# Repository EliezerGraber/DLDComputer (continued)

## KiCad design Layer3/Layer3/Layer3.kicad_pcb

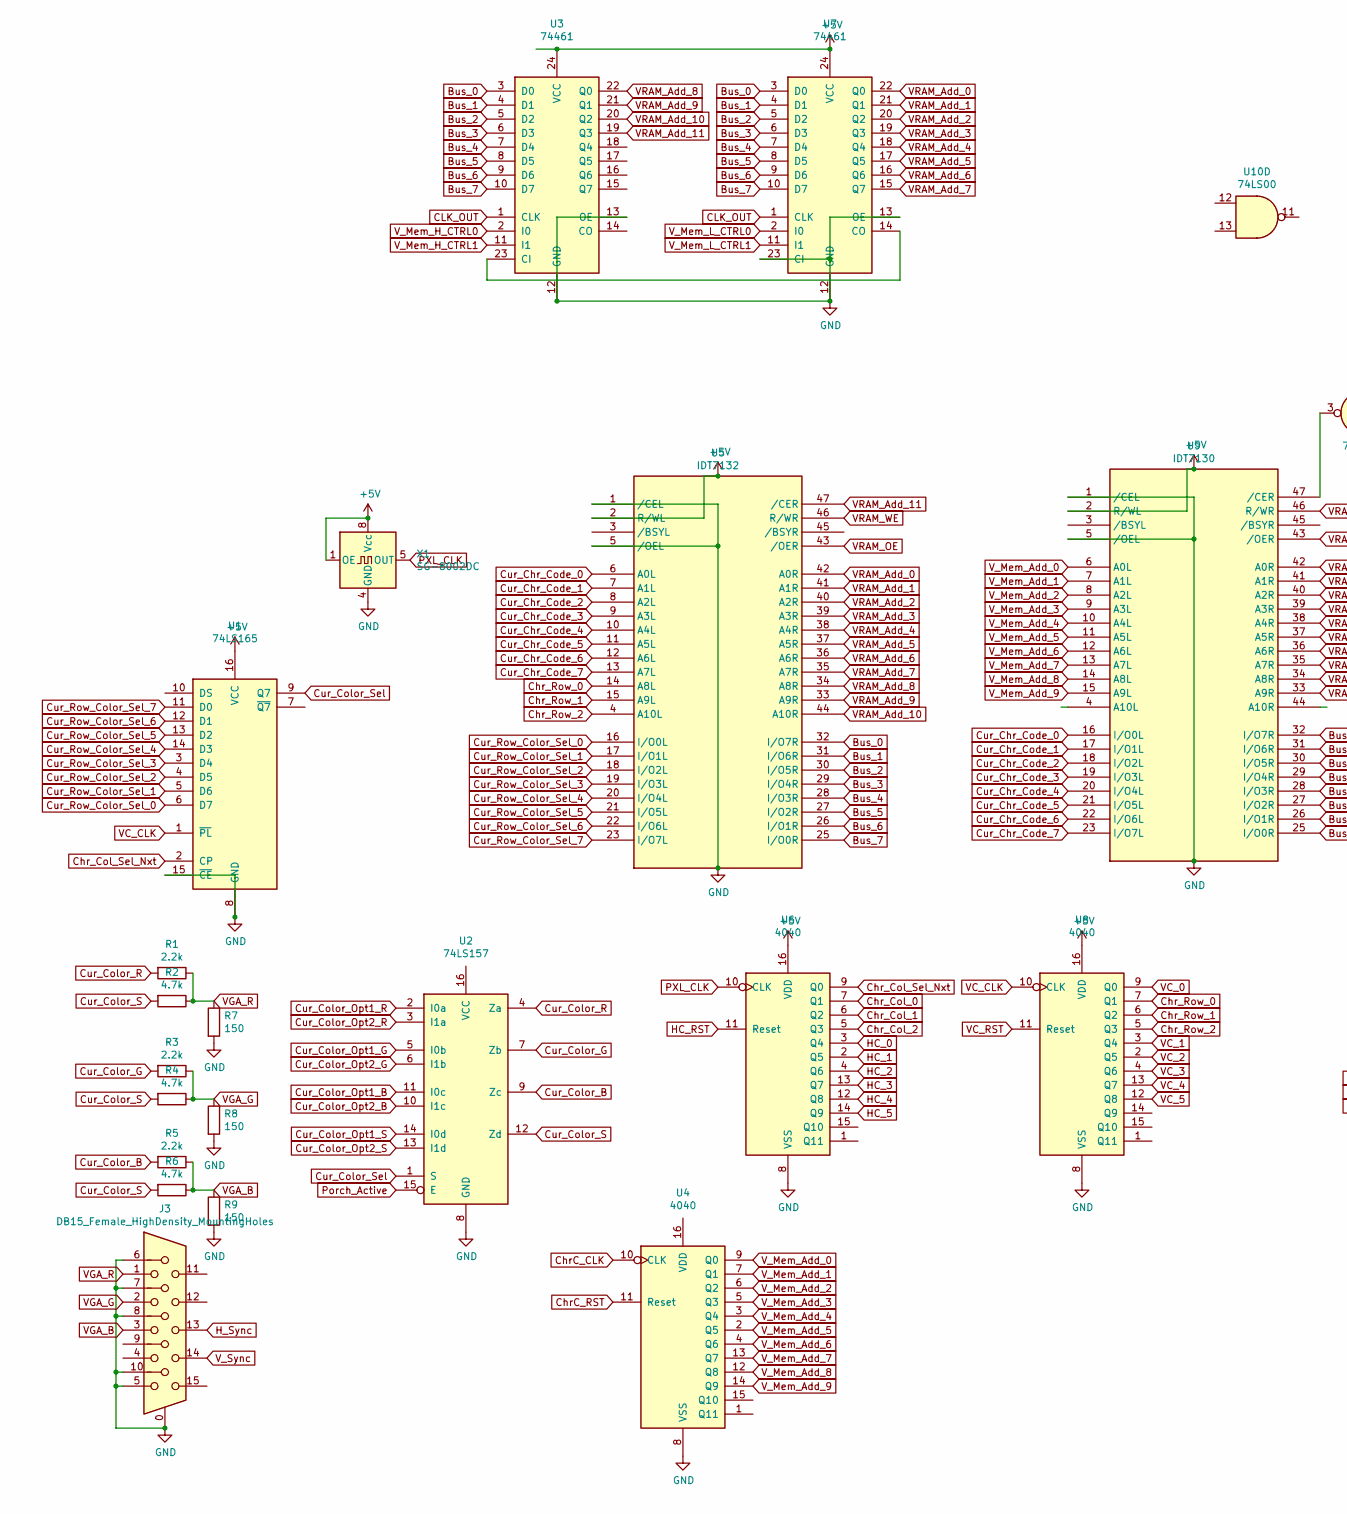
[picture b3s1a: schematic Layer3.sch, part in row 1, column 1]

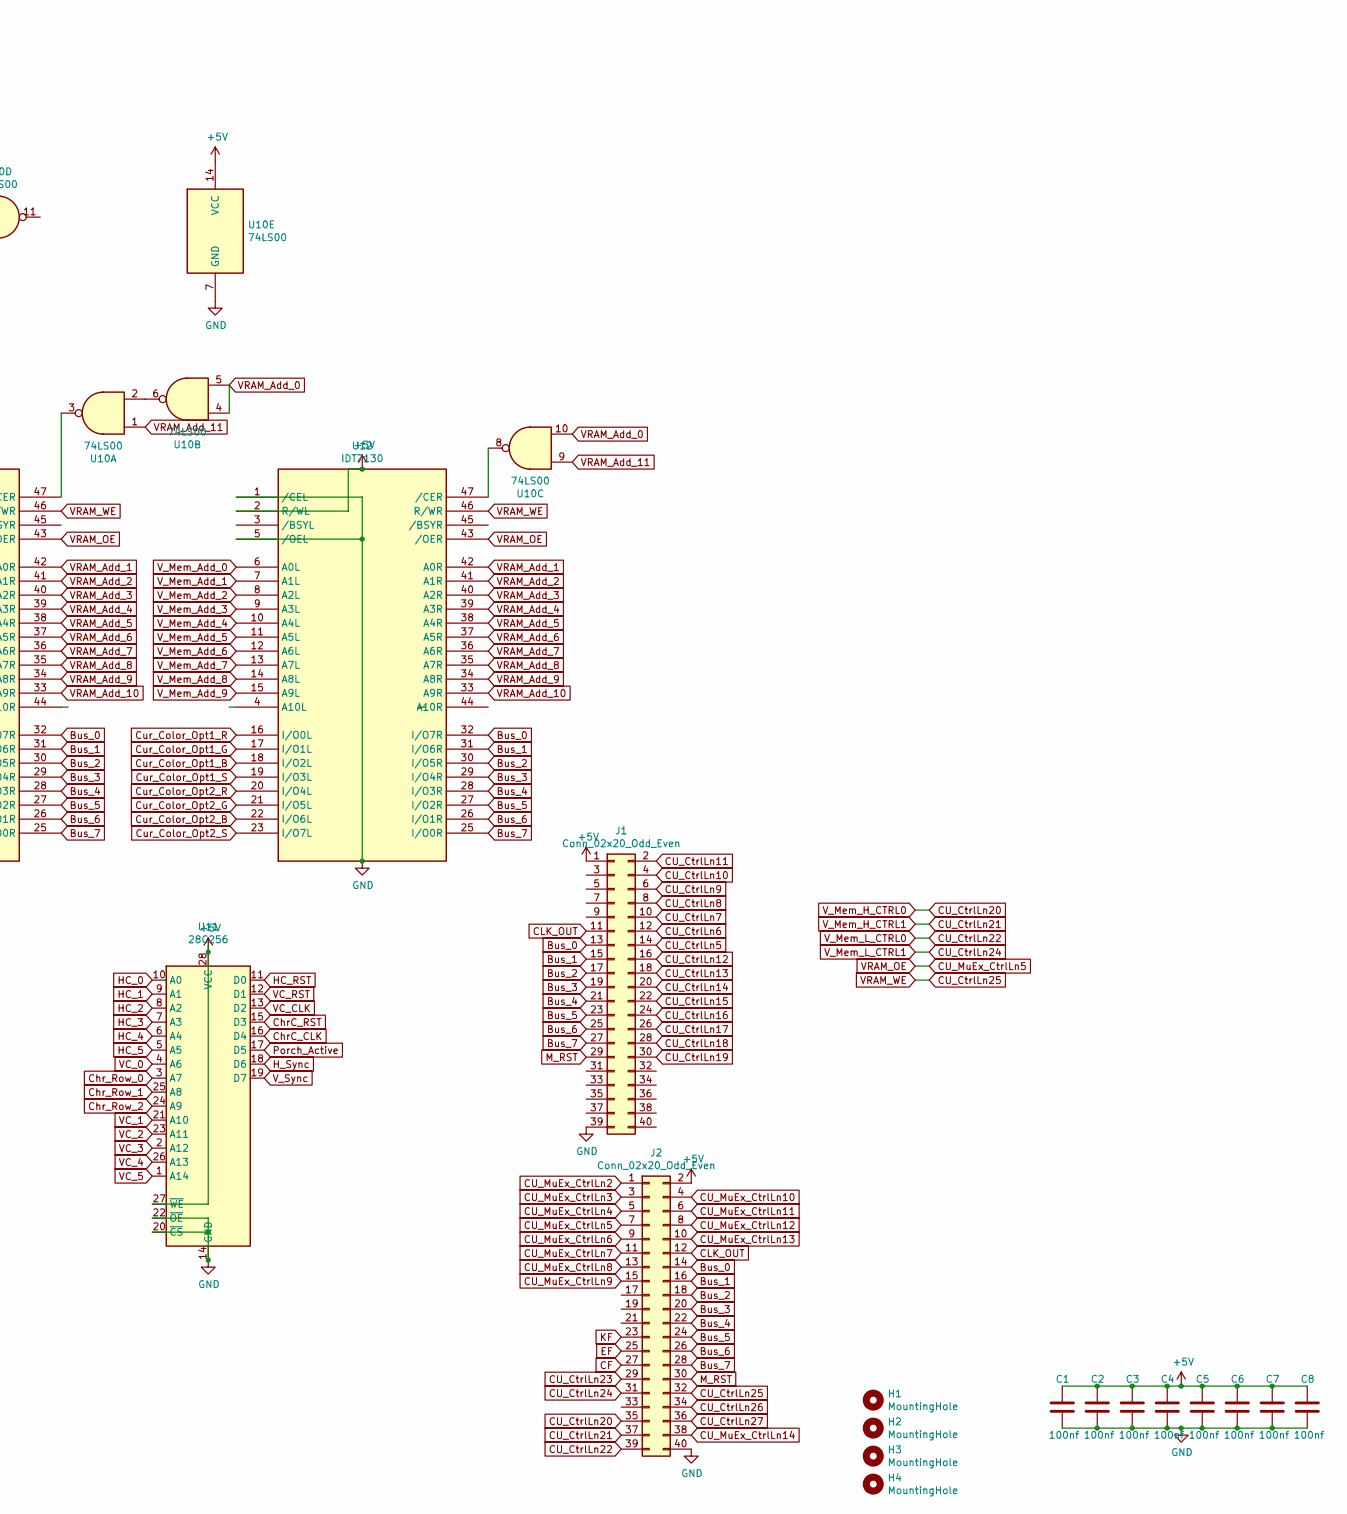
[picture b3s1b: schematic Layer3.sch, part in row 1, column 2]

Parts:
C1, C2, C3, C4, C5, C6, C7, C8: 100nf; C_Disc_D5.0mm_W2.5mm_P2.50mm
H1, H2, H3, H4: MountingHole; MountingHole_4mm
J1, J2: Conn_02x20_Odd_Even; PinHeader_2x20_P2.54mm_Vertical
J3: DB15_Female_HighDensity_MountingHoles
R1, R3, R5: 2.2k; R_Axial_DIN0309_L9.0mm_D3.2mm_P12.70mm_Horizontal
R2, R4, R6: 4.7k; R_Axial_DIN0309_L9.0mm_D3.2mm_P12.70mm_Horizontal
R7, R8, R9: 150; R_Axial_DIN0309_L9.0mm_D3.2mm_P12.70mm_Horizontal
U1: 74LS165; DIP-16_W7.62mm_LongPads
U2: 74LS157; DIP-16_W7.62mm_LongPads
U3, U7: 74461; DIP-24_W7.62mm_LongPads
U4, U6, U8: 4040; DIP-16_W7.62mm_LongPads
U5: IDT7132; DIP-48_W15.24mm_LongPads
U9, U12: IDT7130; DIP-48_W15.24mm_LongPads
U10: 74LS00; DIP-14_W7.62mm_LongPads
U11: 28C256; DIP-28_W15.24mm_LongPads
X1: SG-8002DC; Oscillator_SeikoEpson_SG-8002DC

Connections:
+5V: C1.1, C2.1, C3.1, C4.1, C5.1, C6.1, C7.1, C8.1, J1.1, J2.2, U1.16 (VCC), U3.24 (VCC), U5.2 (R/WL), U5.48 (VCC), U6.16 (VDD), U7.24 (VCC), U8.16 (VDD), U9.2 (R/WL), U9.48 (VCC), U10.14 (VCC), U11.27 (~WE), U11.28 (VCC), U12.2 (R/WL), U12.48 (VCC), X1.1 (OE), X1.8 (Vcc)
Bus_0: J1.13, J2.14, U3.3 (D0), U5.32 (I/O7R), U7.3 (D0), U9.32 (I/O7R), U12.32 (I/O7R)
Bus_1: J1.15, J2.16, U3.4 (D1), U5.31 (I/O6R), U7.4 (D1), U9.31 (I/O6R), U12.31 (I/O6R)
Bus_2: J1.17, J2.18, U3.5 (D2), U5.30 (I/O5R), U7.5 (D2), U9.30 (I/O5R), U12.30 (I/O5R)
Bus_3: J1.19, J2.20, U3.6 (D3), U5.29 (I/O4R), U7.6 (D3), U9.29 (I/O4R), U12.29 (I/O4R)
Bus_4: J1.21, J2.22, U3.7 (D4), U5.28 (I/O3R), U7.7 (D4), U9.28 (I/O3R), U12.28 (I/O3R)
Bus_5: J1.23, J2.24, U3.8 (D5), U5.27 (I/O2R), U7.8 (D5), U9.27 (I/O2R), U12.27 (I/O2R)
Bus_6: J1.25, J2.26, U3.9 (D6), U5.26 (I/O1R), U7.9 (D6), U9.26 (I/O1R), U12.26 (I/O1R)
Bus_7: J1.27, J2.28, U3.10 (D7), U5.25 (I/O0R), U7.10 (D7), U9.25 (I/O0R), U12.25 (I/O0R)
CF: J2.27
CLK_OUT: J1.11, J2.12, U3.1 (CLK), U7.1 (CLK)
CU_CtrlLn5: J1.14
CU_CtrlLn6: J1.12
CU_CtrlLn7: J1.10
CU_CtrlLn8: J1.8
CU_CtrlLn9: J1.6
CU_CtrlLn10: J1.4
CU_CtrlLn11: J1.2
CU_CtrlLn12: J1.16
CU_CtrlLn13: J1.18
CU_CtrlLn14: J1.20
CU_CtrlLn15: J1.22
CU_CtrlLn16: J1.24
CU_CtrlLn17: J1.26
CU_CtrlLn18: J1.28
CU_CtrlLn19: J1.30
CU_CtrlLn20: J2.35, U3.2 (I0)
CU_CtrlLn21: J2.37, U3.11 (I1)
CU_CtrlLn22: J2.39, U7.2 (I0)
CU_CtrlLn23: J2.29
CU_CtrlLn24: J2.31, U7.11 (I1)
CU_CtrlLn25: J2.32, U5.46 (R/WR), U9.46 (R/WR), U12.46 (R/WR)
CU_CtrlLn26: J2.34
CU_CtrlLn27: J2.36
CU_MuEx_CtrlLn2: J2.1
CU_MuEx_CtrlLn3: J2.3
CU_MuEx_CtrlLn4: J2.5
CU_MuEx_CtrlLn5: J2.7, U5.43 (/OER), U9.43 (/OER), U12.43 (/OER)
CU_MuEx_CtrlLn6: J2.9
CU_MuEx_CtrlLn7: J2.11
CU_MuEx_CtrlLn8: J2.13
CU_MuEx_CtrlLn9: J2.15
CU_MuEx_CtrlLn10: J2.4
CU_MuEx_CtrlLn11: J2.6
CU_MuEx_CtrlLn12: J2.8
CU_MuEx_CtrlLn13: J2.10
CU_MuEx_CtrlLn14: J2.38
ChrC_CLK: U4.10 (CLK), U11.16 (D4)
ChrC_RST: U4.11 (Reset), U11.15 (D3)
Chr_Col_0: U6.7 (Q1)
Chr_Col_1: U6.6 (Q2)
Chr_Col_2: U6.5 (Q3)
Chr_Col_Sel_Nxt: U1.2 (CP), U6.9 (Q0)
Chr_Row_0: U5.14 (A8L), U8.7 (Q1), U11.3 (A7)
Chr_Row_1: U5.15 (A9L), U8.6 (Q2), U11.25 (A8)
Chr_Row_2: U5.4 (A10L), U8.5 (Q3), U11.24 (A9)
Cur_Chr_Code_0: U5.6 (A0L), U9.16 (I/O0L)
Cur_Chr_Code_1: U5.7 (A1L), U9.17 (I/O1L)
Cur_Chr_Code_2: U5.8 (A2L), U9.18 (I/O2L)
Cur_Chr_Code_3: U5.9 (A3L), U9.19 (I/O3L)
Cur_Chr_Code_4: U5.10 (A4L), U9.20 (I/O4L)
Cur_Chr_Code_5: U5.11 (A5L), U9.21 (I/O5L)
Cur_Chr_Code_6: U5.12 (A6L), U9.22 (I/O6L)
Cur_Chr_Code_7: U5.13 (A7L), U9.23 (I/O7L)
Cur_Color_B: R5.2, U2.9 (Zc)
Cur_Color_G: R3.2, U2.7 (Zb)
Cur_Color_Opt1_B: U2.11 (I0c), U12.18 (I/O2L)
Cur_Color_Opt1_G: U2.5 (I0b), U12.17 (I/O1L)
Cur_Color_Opt1_R: U2.2 (I0a), U12.16 (I/O0L)
Cur_Color_Opt1_S: U2.14 (I0d), U12.19 (I/O3L)
Cur_Color_Opt2_B: U2.10 (I1c), U12.22 (I/O6L)
Cur_Color_Opt2_G: U2.6 (I1b), U12.21 (I/O5L)
Cur_Color_Opt2_R: U2.3 (I1a), U12.20 (I/O4L)
Cur_Color_Opt2_S: U2.13 (I1d), U12.23 (I/O7L)
Cur_Color_R: R1.2, U2.4 (Za)
Cur_Color_S: R2.2, R4.2, R6.2, U2.12 (Zd)
Cur_Color_Sel: U1.9 (Q7), U2.1 (S)
Cur_Row_Color_Sel_0: U1.6 (D7), U5.16 (I/O0L)
Cur_Row_Color_Sel_1: U1.5 (D6), U5.17 (I/O1L)
Cur_Row_Color_Sel_2: U1.4 (D5), U5.18 (I/O2L)
Cur_Row_Color_Sel_3: U1.3 (D4), U5.19 (I/O3L)
Cur_Row_Color_Sel_4: U1.14 (D3), U5.20 (I/O4L)
Cur_Row_Color_Sel_5: U1.13 (D2), U5.21 (I/O5L)
Cur_Row_Color_Sel_6: U1.12 (D1), U5.22 (I/O6L)
Cur_Row_Color_Sel_7: U1.11 (D0), U5.23 (I/O7L)
EF: J2.25
GND: C1.2, C2.2, C3.2, C4.2, C5.2, C6.2, C7.2, C8.2, J1.39, J2.40, J3.0, J3.5, J3.6, J3.7, J3.8, J3.10, R7.2, R8.2, R9.2, U1.8 (GND), U1.15 (~CE), U2.8 (GND), U3.12 (GND), U3.13 (OE), U4.8 (VSS), U5.1 (/CEL), U5.5 (/OEL), U5.24 (GND), U6.8 (VSS), U7.12 (GND), U7.13 (OE), U7.23 (CI), U8.8 (VSS), U9.1 (/CEL), U9.5 (/OEL), U9.24 (GND), U10.7 (GND), U11.14 (GND), U11.20 (~CS), U11.22 (~OE), U12.1 (/CEL), U12.5 (/OEL), U12.24 (GND), X1.4 (GND)
HC_0: U6.3 (Q4), U11.10 (A0)
HC_1: U6.2 (Q5), U11.9 (A1)
HC_2: U6.4 (Q6), U11.8 (A2)
HC_3: U6.13 (Q7), U11.7 (A3)
HC_4: U6.12 (Q8), U11.6 (A4)
HC_5: U6.14 (Q9), U11.5 (A5)
HC_RST: U6.11 (Reset), U11.11 (D0)
H_Sync: J3.13, U11.18 (D6)
KF: J2.23
M_RST: J1.29, J2.30
unnamed: U3.23 (CI), U7.14 (CO)
unnamed: U10.2, U10.6
unnamed: U9.47 (/CER), U10.3
unnamed: U10.8, U12.47 (/CER)
PXL_CLK: U6.10 (CLK), X1.5 (OUT)
Porch_Active: U2.15 (E), U11.17 (D5)
VC_0: U8.9 (Q0), U11.4 (A6)
VC_1: U8.3 (Q4), U11.21 (A10)
VC_2: U8.2 (Q5), U11.23 (A11)
VC_3: U8.4 (Q6), U11.2 (A12)
VC_4: U8.13 (Q7), U11.26 (A13)
VC_5: U8.12 (Q8), U11.1 (A14)
VC_CLK: U1.1 (~PL), U8.10 (CLK), U11.13 (D2)
VC_RST: U8.11 (Reset), U11.12 (D1)
VGA_B: J3.3, R5.1, R6.1, R9.1
VGA_G: J3.2, R3.1, R4.1, R8.1
VGA_R: J3.1, R1.1, R2.1, R7.1
VRAM_Add_0: U5.42 (A0R), U7.22 (Q0), U10.4, U10.5, U10.10
VRAM_Add_1: U5.41 (A1R), U7.21 (Q1), U9.42 (A0R), U12.42 (A0R)
VRAM_Add_2: U5.40 (A2R), U7.20 (Q2), U9.41 (A1R), U12.41 (A1R)
VRAM_Add_3: U5.39 (A3R), U7.19 (Q3), U9.40 (A2R), U12.40 (A2R)
VRAM_Add_4: U5.38 (A4R), U7.18 (Q4), U9.39 (A3R), U12.39 (A3R)
VRAM_Add_5: U5.37 (A5R), U7.17 (Q5), U9.38 (A4R), U12.38 (A4R)
VRAM_Add_6: U5.36 (A6R), U7.16 (Q6), U9.37 (A5R), U12.37 (A5R)
VRAM_Add_7: U5.35 (A7R), U7.15 (Q7), U9.36 (A6R), U12.36 (A6R)
VRAM_Add_8: U3.22 (Q0), U5.34 (A8R), U9.35 (A7R), U12.35 (A7R)
VRAM_Add_9: U3.21 (Q1), U5.33 (A9R), U9.34 (A8R), U12.34 (A8R)
VRAM_Add_10: U3.20 (Q2), U5.44 (A10R), U9.33 (A9R), U12.33 (A9R)
VRAM_Add_11: U3.19 (Q3), U5.47 (/CER), U10.1, U10.9
V_Mem_Add_0: U4.9 (Q0), U9.6 (A0L), U12.6 (A0L)
V_Mem_Add_1: U4.7 (Q1), U9.7 (A1L), U12.7 (A1L)
V_Mem_Add_2: U4.6 (Q2), U9.8 (A2L), U12.8 (A2L)
V_Mem_Add_3: U4.5 (Q3), U9.9 (A3L), U12.9 (A3L)
V_Mem_Add_4: U4.3 (Q4), U9.10 (A4L), U12.10 (A4L)
V_Mem_Add_5: U4.2 (Q5), U9.11 (A5L), U12.11 (A5L)
V_Mem_Add_6: U4.4 (Q6), U9.12 (A6L), U12.12 (A6L)
V_Mem_Add_7: U4.13 (Q7), U9.13 (A7L), U12.13 (A7L)
V_Mem_Add_8: U4.12 (Q8), U9.14 (A8L), U12.14 (A8L)
V_Mem_Add_9: U4.14 (Q9), U9.15 (A9L), U12.15 (A9L)
V_Sync: J3.14, U11.19 (D7)

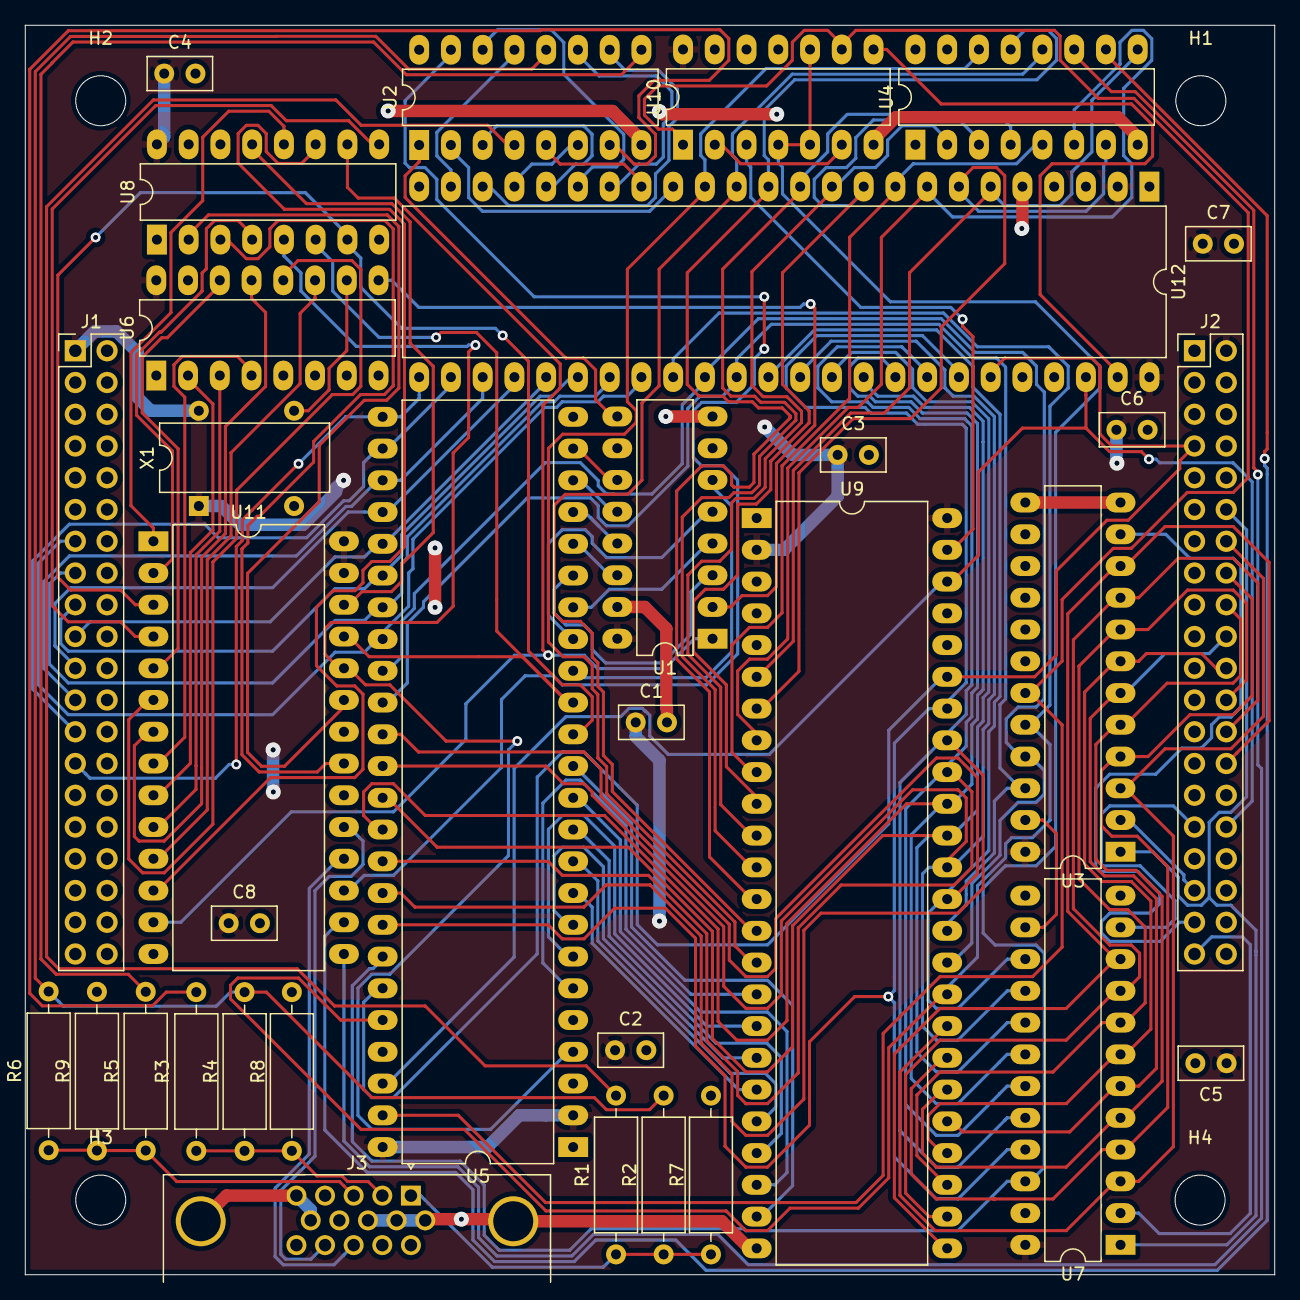
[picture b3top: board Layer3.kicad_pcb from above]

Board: 2 copper layers, 99.9 x 99.9 mm, 37 parts (0 on the bottom side), 101 nets.

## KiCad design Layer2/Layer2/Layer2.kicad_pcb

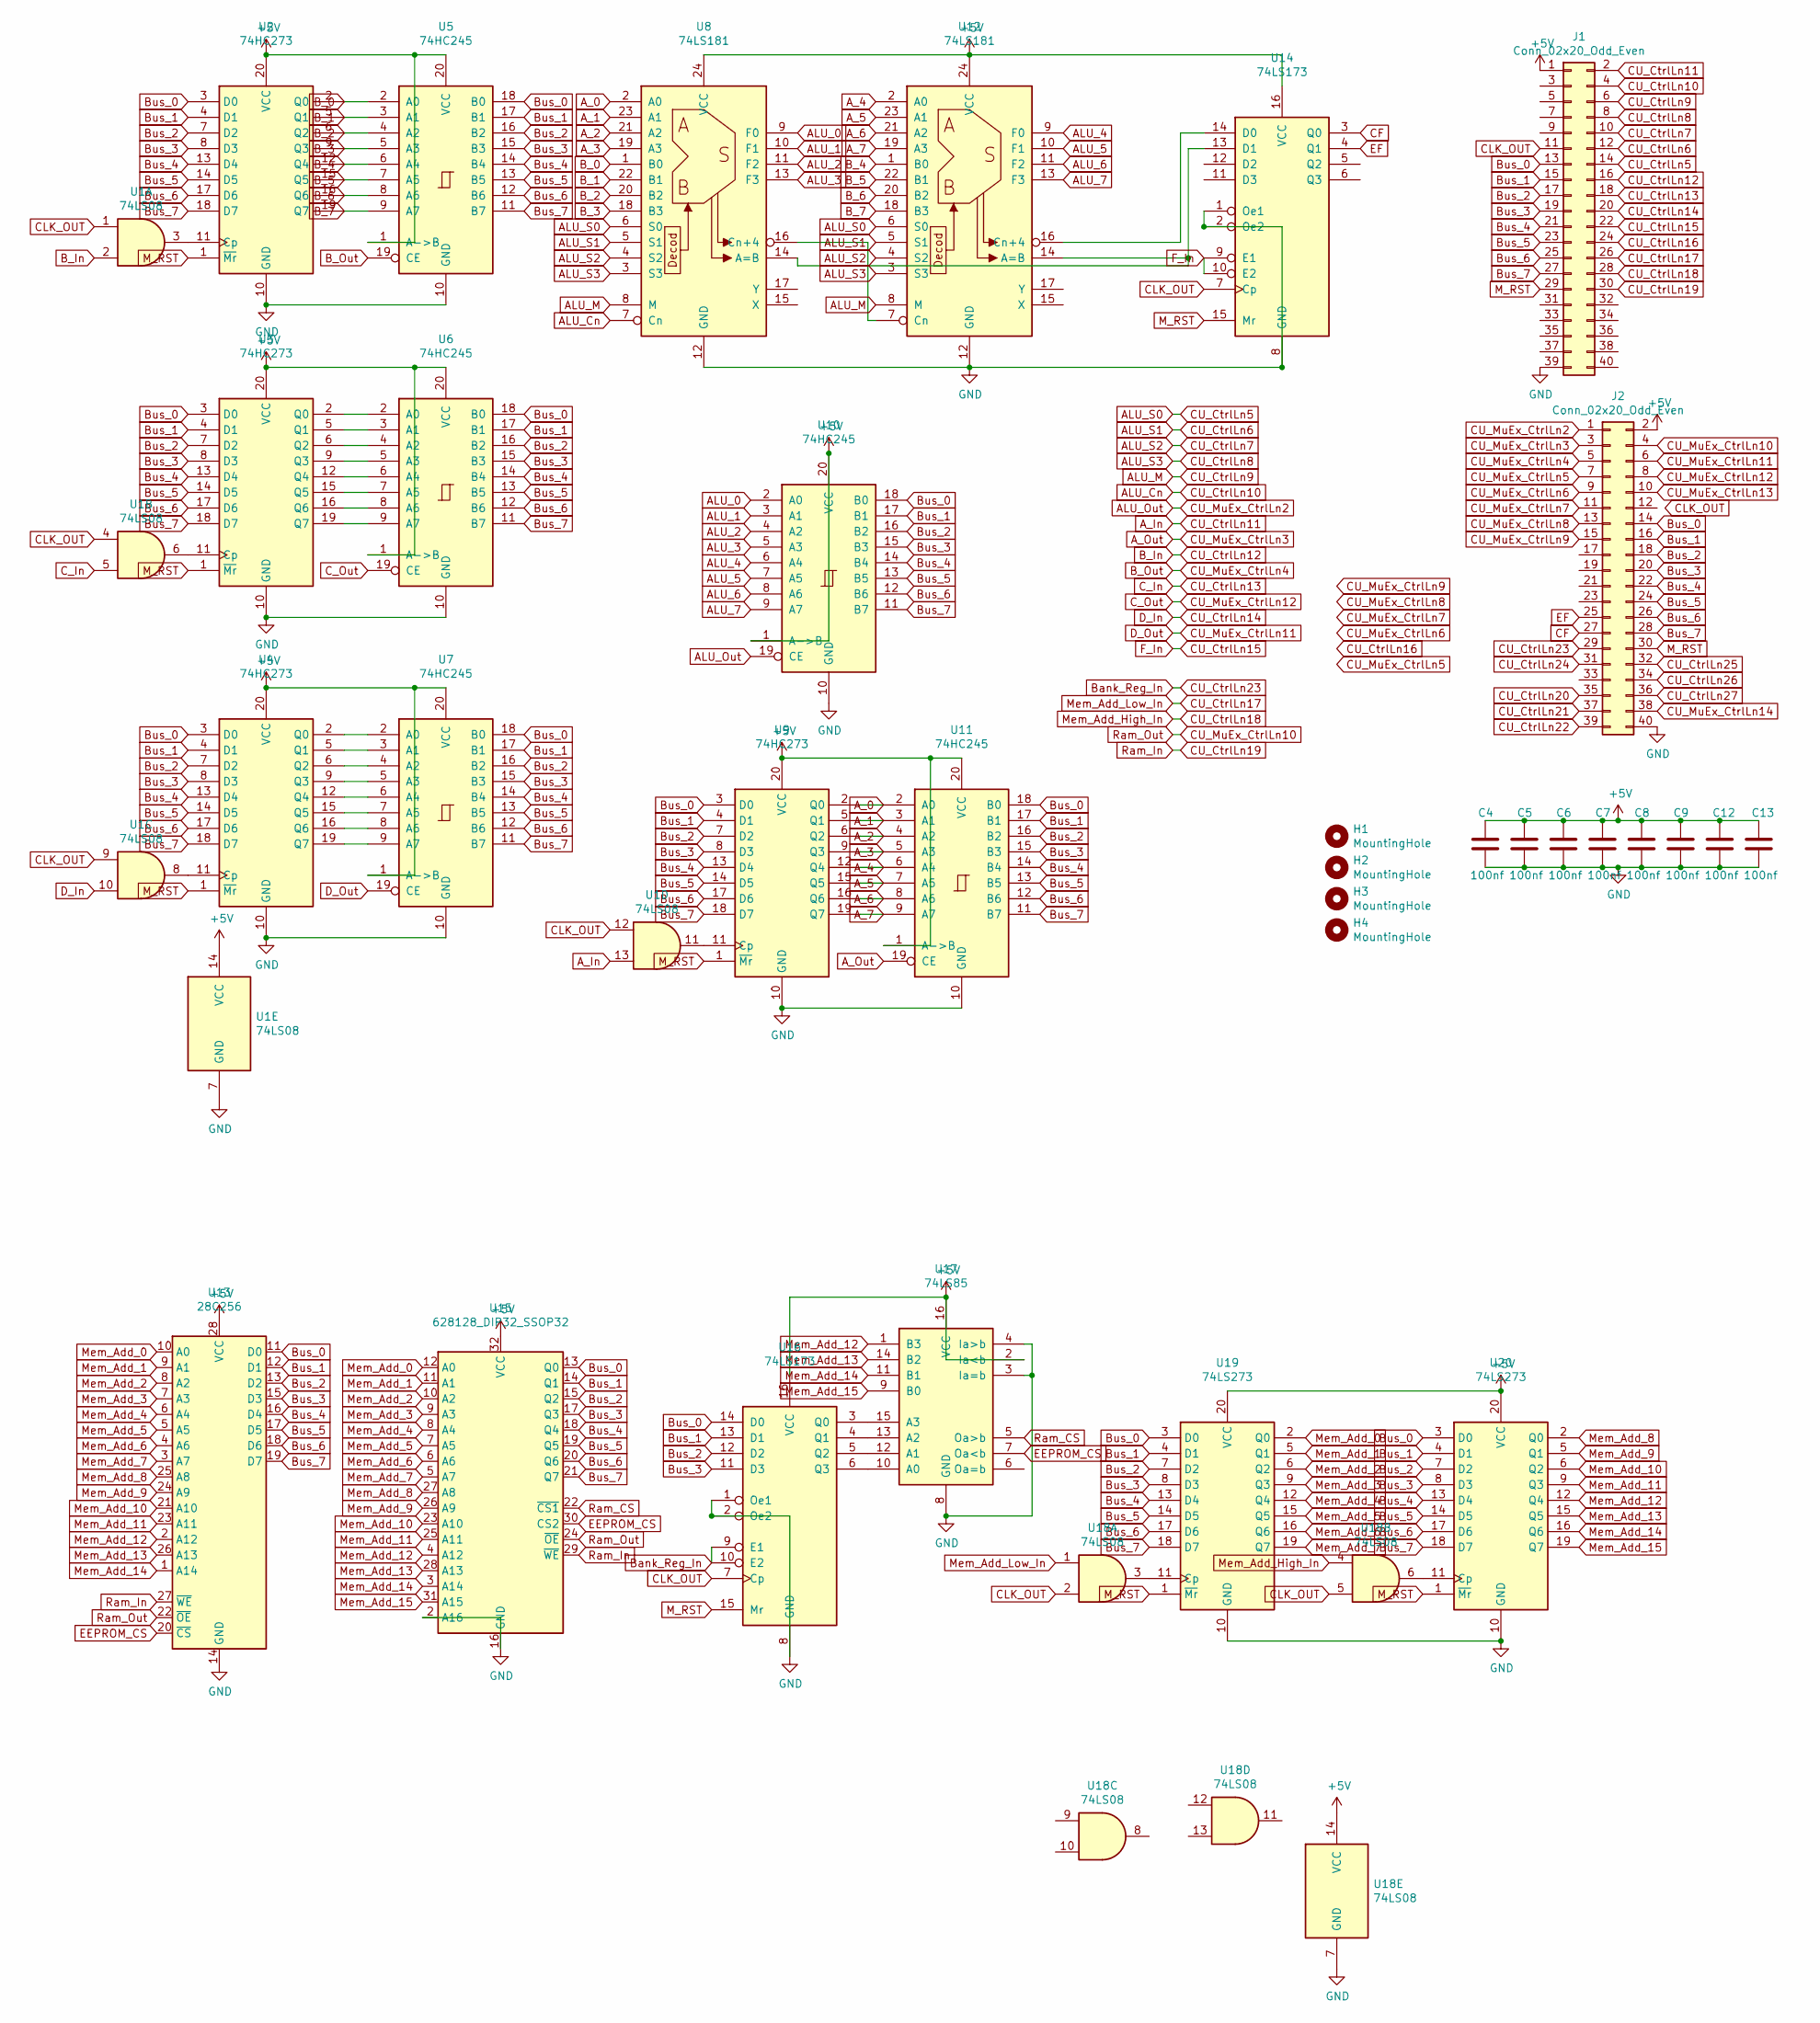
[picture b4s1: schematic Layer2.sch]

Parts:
C4, C5, C6, C7, C8, C9, C12, C13: 100nf; C_Disc_D5.0mm_W2.5mm_P2.50mm
H1, H2, H3, H4: MountingHole; MountingHole_4mm
J1, J2: Conn_02x20_Odd_Even; PinHeader_2x20_P2.54mm_Vertical
U1, U18: 74LS08; DIP-14_W7.62mm_LongPads
U2, U3, U4, U9: 74HC273; DIP-20_W7.62mm_LongPads
U5, U6, U7, U10, U11: 74HC245; DIP-20_W7.62mm_LongPads
U8, U12: 74LS181; DIP-24_W15.24mm_LongPads
U13: 28C256; DIP-28_W15.24mm_LongPads
U14, U16: 74LS173; DIP-16_W7.62mm_LongPads
U15: 628128_DIP32_SSOP32; DIP-32_W15.24mm_LongPads
U17: 74LS85; DIP-16_W7.62mm_LongPads
U19, U20: 74LS273; DIP-20_W7.62mm_LongPads

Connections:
+5V: C4.1, C5.1, C6.1, C7.1, C8.1, C9.1, C12.1, C13.1, J1.1, J2.2, U1.14 (VCC), U2.20 (VCC), U3.20 (VCC), U4.20 (VCC), U5.1 (A->B), U5.20 (VCC), U6.1 (A->B), U6.20 (VCC), U7.1 (A->B), U7.20 (VCC), U8.24 (VCC), U9.20 (VCC), U10.1 (A->B), U10.20 (VCC), U11.1 (A->B), U11.20 (VCC), U12.24 (VCC), U13.28 (VCC), U14.16 (VCC), U15.32 (VCC), U16.16 (VCC), U17.2 (Ia<b), U17.16 (VCC), U18.14 (VCC), U19.20 (VCC), U20.20 (VCC)
ALU_0: U8.9 (F0), U10.2 (A0)
ALU_1: U8.10 (F1), U10.3 (A1)
ALU_2: U8.11 (F2), U10.4 (A2)
ALU_3: U8.13 (F3), U10.5 (A3)
ALU_4: U10.6 (A4), U12.9 (F0)
ALU_5: U10.7 (A5), U12.10 (F1)
ALU_6: U10.8 (A6), U12.11 (F2)
ALU_7: U10.9 (A7), U12.13 (F3)
ALU_Cn: J1.4, U8.7 (Cn)
ALU_M: J1.6, U8.8 (M), U12.8 (M)
ALU_Out: J2.1, U10.19 (CE)
ALU_S0: J1.14, U8.6 (S0), U12.6 (S0)
ALU_S1: J1.12, U8.5 (S1), U12.5 (S1)
ALU_S2: J1.10, U8.4 (S2), U12.4 (S2)
ALU_S3: J1.8, U8.3 (S3), U12.3 (S3)
A_0: U8.2 (A0), U9.2 (Q0), U11.2 (A0)
A_1: U8.23 (A1), U9.5 (Q1), U11.3 (A1)
A_2: U8.21 (A2), U9.6 (Q2), U11.4 (A2)
A_3: U8.19 (A3), U9.9 (Q3), U11.5 (A3)
A_4: U9.12 (Q4), U11.6 (A4), U12.2 (A0)
A_5: U9.15 (Q5), U11.7 (A5), U12.23 (A1)
A_6: U9.16 (Q6), U11.8 (A6), U12.21 (A2)
A_7: U9.19 (Q7), U11.9 (A7), U12.19 (A3)
A_In: J1.2, U1.13
A_Out: J2.3, U11.19 (CE)
B_0: U2.2 (Q0), U5.2 (A0), U8.1 (B0)
B_1: U2.5 (Q1), U5.3 (A1), U8.22 (B1)
B_2: U2.6 (Q2), U5.4 (A2), U8.20 (B2)
B_3: U2.9 (Q3), U5.5 (A3), U8.18 (B3)
B_4: U2.12 (Q4), U5.6 (A4), U12.1 (B0)
B_5: U2.15 (Q5), U5.7 (A5), U12.22 (B1)
B_6: U2.16 (Q6), U5.8 (A6), U12.20 (B2)
B_7: U2.19 (Q7), U5.9 (A7), U12.18 (B3)
B_In: J1.16, U1.2
B_Out: J2.5, U5.19 (CE)
Bank_Reg_In: J2.29, U16.9 (E1), U16.10 (E2)
Bus_0: J1.13, J2.14, U2.3 (D0), U3.3 (D0), U4.3 (D0), U5.18 (B0), U6.18 (B0), U7.18 (B0), U9.3 (D0), U10.18 (B0), U11.18 (B0), U13.11 (D0), U15.13 (Q0), U16.14 (D0), U19.3 (D0), U20.3 (D0)
Bus_1: J1.15, J2.16, U2.4 (D1), U3.4 (D1), U4.4 (D1), U5.17 (B1), U6.17 (B1), U7.17 (B1), U9.4 (D1), U10.17 (B1), U11.17 (B1), U13.12 (D1), U15.14 (Q1), U16.13 (D1), U19.4 (D1), U20.4 (D1)
Bus_2: J1.17, J2.18, U2.7 (D2), U3.7 (D2), U4.7 (D2), U5.16 (B2), U6.16 (B2), U7.16 (B2), U9.7 (D2), U10.16 (B2), U11.16 (B2), U13.13 (D2), U15.15 (Q2), U16.12 (D2), U19.7 (D2), U20.7 (D2)
Bus_3: J1.19, J2.20, U2.8 (D3), U3.8 (D3), U4.8 (D3), U5.15 (B3), U6.15 (B3), U7.15 (B3), U9.8 (D3), U10.15 (B3), U11.15 (B3), U13.15 (D3), U15.17 (Q3), U16.11 (D3), U19.8 (D3), U20.8 (D3)
Bus_4: J1.21, J2.22, U2.13 (D4), U3.13 (D4), U4.13 (D4), U5.14 (B4), U6.14 (B4), U7.14 (B4), U9.13 (D4), U10.14 (B4), U11.14 (B4), U13.16 (D4), U15.18 (Q4), U19.13 (D4), U20.13 (D4)
Bus_5: J1.23, J2.24, U2.14 (D5), U3.14 (D5), U4.14 (D5), U5.13 (B5), U6.13 (B5), U7.13 (B5), U9.14 (D5), U10.13 (B5), U11.13 (B5), U13.17 (D5), U15.19 (Q5), U19.14 (D5), U20.14 (D5)
Bus_6: J1.25, J2.26, U2.17 (D6), U3.17 (D6), U4.17 (D6), U5.12 (B6), U6.12 (B6), U7.12 (B6), U9.17 (D6), U10.12 (B6), U11.12 (B6), U13.18 (D6), U15.20 (Q6), U19.17 (D6), U20.17 (D6)
Bus_7: J1.27, J2.28, U2.18 (D7), U3.18 (D7), U4.18 (D7), U5.11 (B7), U6.11 (B7), U7.11 (B7), U9.18 (D7), U10.11 (B7), U11.11 (B7), U13.19 (D7), U15.21 (Q7), U19.18 (D7), U20.18 (D7)
CF: J2.27, U14.3 (Q0)
CLK_OUT: J1.11, U1.1, U1.4, U1.9, U1.12, U14.7 (Cp), U16.7 (Cp), U18.2, U18.5
CU_CtrlLn13: J1.18, U1.5
CU_CtrlLn14: J1.20, U1.10
CU_CtrlLn15: J1.22, U14.9 (E1), U14.10 (E2)
CU_CtrlLn16: J1.24
CU_CtrlLn17: J1.26, U18.1
CU_CtrlLn18: J1.28, U18.4
CU_CtrlLn19: J1.30, U13.27 (~WE), U15.29 (~WE)
CU_CtrlLn20: J2.35
CU_CtrlLn21: J2.37
CU_CtrlLn22: J2.39
CU_CtrlLn24: J2.31
CU_CtrlLn25: J2.32
CU_CtrlLn26: J2.34
CU_CtrlLn27: J2.36
CU_MuEx_CtrlLn5: J2.7
CU_MuEx_CtrlLn6: J2.9
CU_MuEx_CtrlLn7: J2.11
CU_MuEx_CtrlLn8: J2.13
CU_MuEx_CtrlLn9: J2.15
CU_MuEx_CtrlLn10: J2.4, U13.22 (~OE), U15.24 (~OE)
CU_MuEx_CtrlLn11: J2.6, U7.19 (CE)
CU_MuEx_CtrlLn12: J2.8, U6.19 (CE)
CU_MuEx_CtrlLn13: J2.10
CU_MuEx_CtrlLn14: J2.38
EEPROM_CS: U13.20 (~CS), U15.30 (CS2), U17.7 (Oa<b)
EF: J2.25, U14.4 (Q1)
GND: C4.2, C5.2, C6.2, C7.2, C8.2, C9.2, C12.2, C13.2, J1.39, J2.40, U1.7 (GND), U2.10 (GND), U3.10 (GND), U4.10 (GND), U5.10 (GND), U6.10 (GND), U7.10 (GND), U8.12 (GND), U9.10 (GND), U10.10 (GND), U11.10 (GND), U12.12 (GND), U13.14 (GND), U14.1 (Oe1), U14.2 (Oe2), U14.8 (GND), U15.2 (A16), U15.16 (GND), U16.1 (Oe1), U16.2 (Oe2), U16.8 (GND), U17.3 (Ia=b), U17.4 (Ia>b), U17.8 (GND), U18.7 (GND), U19.10 (GND), U20.10 (GND)
M_RST: J1.29, J2.30, U2.1 (~Mr), U3.1 (~Mr), U4.1 (~Mr), U9.1 (~Mr), U14.15 (Mr), U16.15 (Mr), U19.1 (~Mr), U20.1 (~Mr)
Mem_Add_0: U13.10 (A0), U15.12 (A0), U19.2 (Q0)
Mem_Add_1: U13.9 (A1), U15.11 (A1), U19.5 (Q1)
Mem_Add_2: U13.8 (A2), U15.10 (A2), U19.6 (Q2)
Mem_Add_3: U13.7 (A3), U15.9 (A3), U19.9 (Q3)
Mem_Add_4: U13.6 (A4), U15.8 (A4), U19.12 (Q4)
Mem_Add_5: U13.5 (A5), U15.7 (A5), U19.15 (Q5)
Mem_Add_6: U13.4 (A6), U15.6 (A6), U19.16 (Q6)
Mem_Add_7: U13.3 (A7), U15.5 (A7), U19.19 (Q7)
Mem_Add_8: U13.25 (A8), U15.27 (A8), U20.2 (Q0)
Mem_Add_9: U13.24 (A9), U15.26 (A9), U20.5 (Q1)
Mem_Add_10: U13.21 (A10), U15.23 (A10), U20.6 (Q2)
Mem_Add_11: U13.23 (A11), U15.25 (A11), U20.9 (Q3)
Mem_Add_12: U13.2 (A12), U15.4 (A12), U17.1 (B3), U20.12 (Q4)
Mem_Add_13: U13.26 (A13), U15.28 (A13), U17.14 (B2), U20.15 (Q5)
Mem_Add_14: U13.1 (A14), U15.3 (A14), U17.11 (B1), U20.16 (Q6)
Mem_Add_15: U15.31 (A15), U17.9 (B0), U20.19 (Q7)
unnamed: U1.3, U2.11 (Cp)
unnamed: U1.6, U3.11 (Cp)
unnamed: U1.8, U4.11 (Cp)
unnamed: U1.11, U9.11 (Cp)
unnamed: U3.2 (Q0), U6.2 (A0)
unnamed: U3.5 (Q1), U6.3 (A1)
unnamed: U3.6 (Q2), U6.4 (A2)
unnamed: U3.9 (Q3), U6.5 (A3)
unnamed: U3.12 (Q4), U6.6 (A4)
unnamed: U3.15 (Q5), U6.7 (A5)
unnamed: U3.16 (Q6), U6.8 (A6)
unnamed: U3.19 (Q7), U6.9 (A7)
unnamed: U4.2 (Q0), U7.2 (A0)
unnamed: U4.5 (Q1), U7.3 (A1)
unnamed: U4.6 (Q2), U7.4 (A2)
unnamed: U4.9 (Q3), U7.5 (A3)
unnamed: U4.12 (Q4), U7.6 (A4)
unnamed: U4.15 (Q5), U7.7 (A5)
unnamed: U4.16 (Q6), U7.8 (A6)
unnamed: U4.19 (Q7), U7.9 (A7)
unnamed: U8.16 (Cn+4), U12.7 (Cn)
unnamed: U8.14 (A=B), U12.14 (A=B), U14.13 (D1)
unnamed: U12.16 (Cn+4), U14.14 (D0)
unnamed: U16.3 (Q0), U17.15 (A3)
unnamed: U16.4 (Q1), U17.13 (A2)
unnamed: U16.5 (Q2), U17.12 (A1)
unnamed: U16.6 (Q3), U17.10 (A0)
unnamed: U18.3, U19.11 (Cp)
unnamed: U18.6, U20.11 (Cp)
Ram_CS: U15.22 (~CS1), U17.5 (Oa>b)

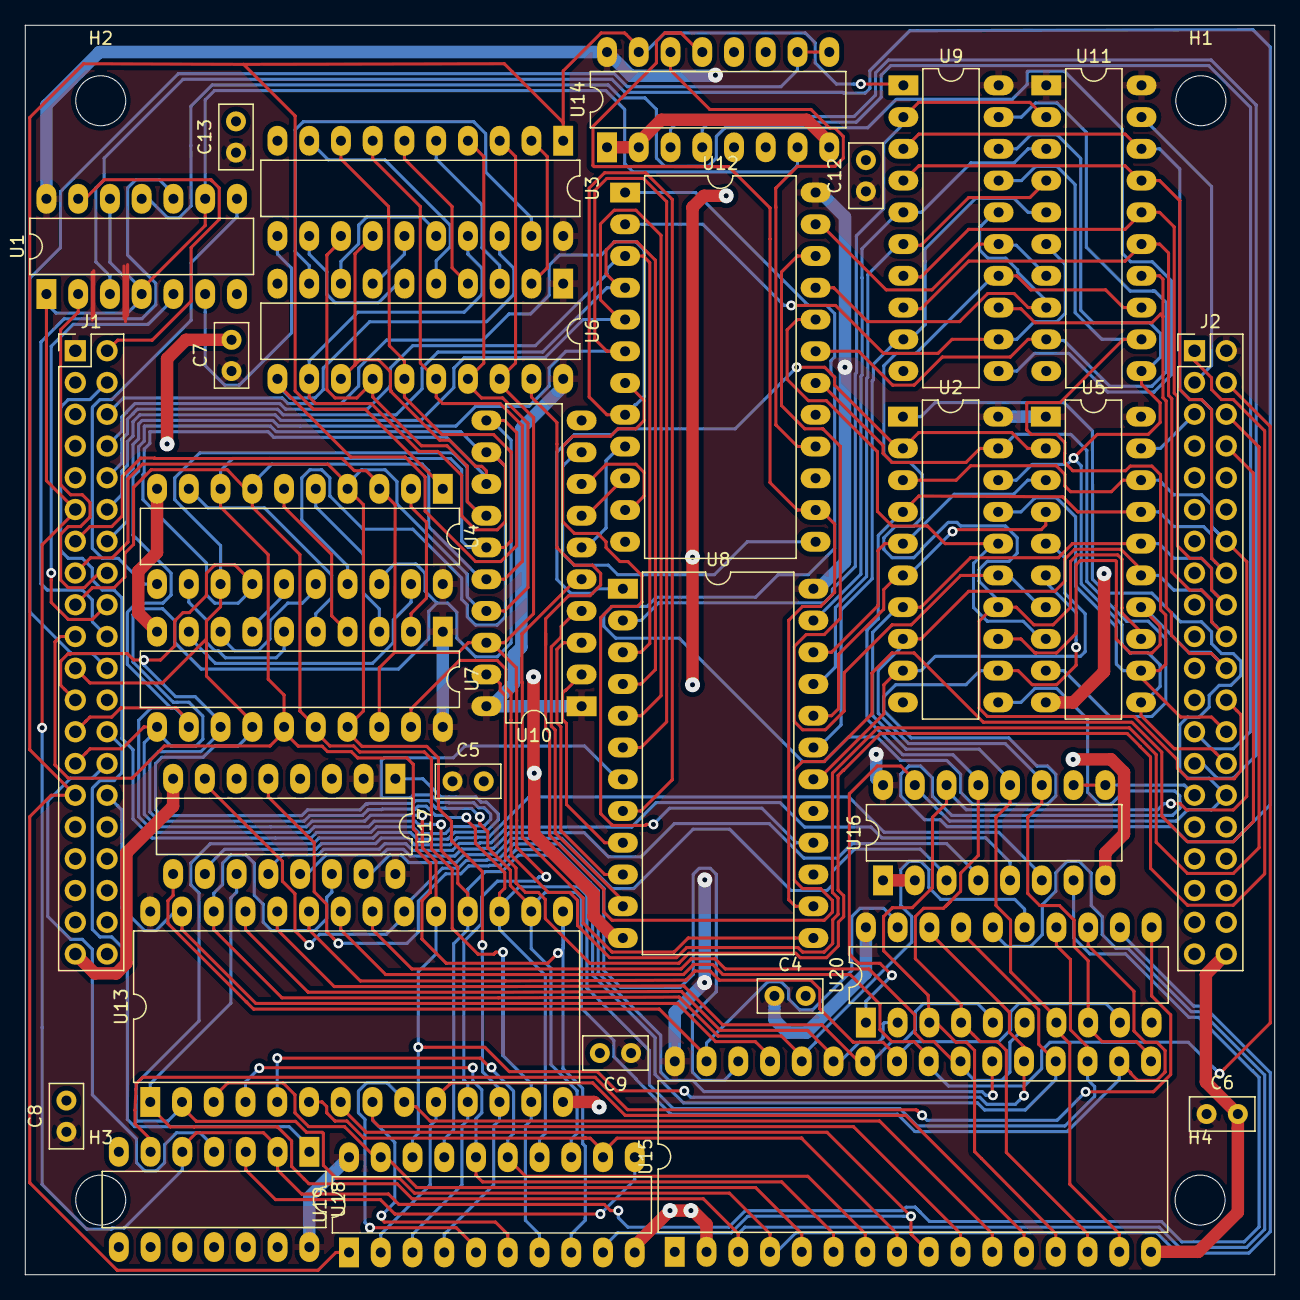
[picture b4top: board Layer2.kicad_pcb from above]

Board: 2 copper layers, 99.9 x 99.9 mm, 34 parts (0 on the bottom side), 106 nets.

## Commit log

2022-03-30 Init commit
2022-04-11 Finished Layer1
2022-04-25 Layer2 Progress
2022-07-21 Layer 3 complete
2022-08-01 Backup
